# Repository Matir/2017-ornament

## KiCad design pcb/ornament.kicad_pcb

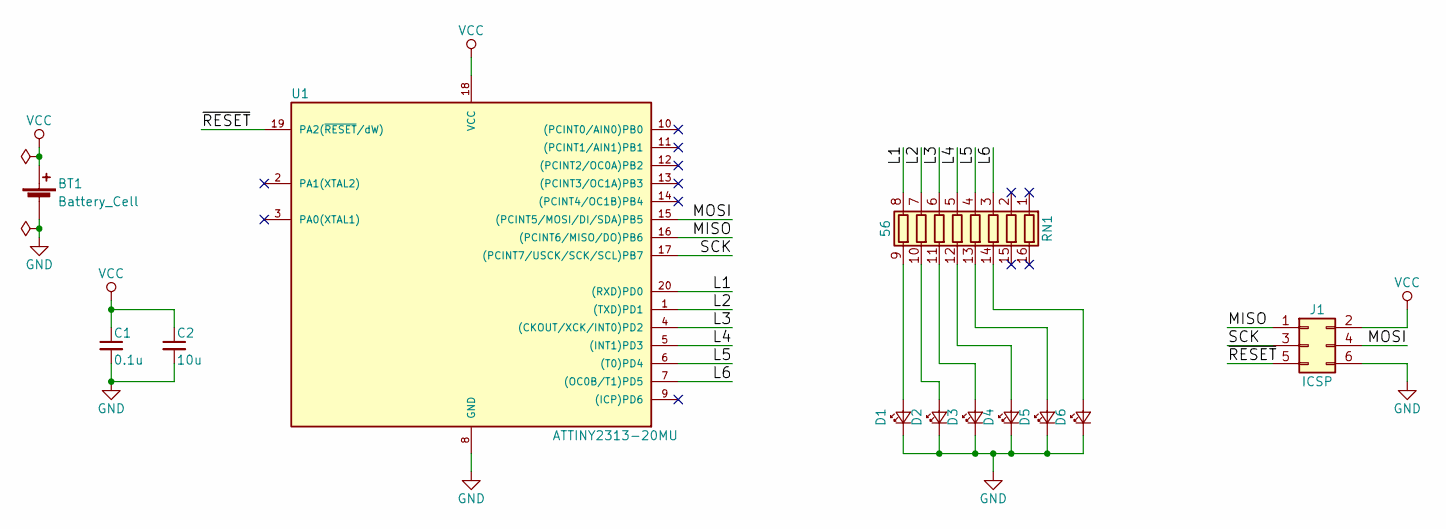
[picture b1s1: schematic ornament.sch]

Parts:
BT1: Battery_Cell; BAT_HLD
C1: 0.1u; C_0805
C2: 10u; C_0805
D1, D2, D3, D4, D5, D6: LED_Small; LED_0805
J1: ICSP; Pin_Header_Straight_2x03_Pitch2.54mm_SMD
RN1: 56; R_Array_Convex_8x0602
U1: ATTINY2313-20MU; QFN-20-1EP_4x4mm_Pitch0.5mm

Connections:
/L1: RN1.8 (R8.1), U1.20 ((RXD)PD0)
/L2: RN1.7 (R7.1), U1.1 ((TXD)PD1)
/L3: RN1.6 (R6.1), U1.4 ((CKOUT/XCK/INT0)PD2)
/L4: RN1.5 (R5.1), U1.5 ((INT1)PD3)
/L5: RN1.4 (R4.1), U1.6 ((T0)PD4)
/L6: RN1.3 (R3.1), U1.7 ((OC0B/T1)PD5)
/MISO: J1.1, U1.16 ((PCINT6/MISO/DO)PB6)
/MOSI: J1.4, U1.15 ((PCINT5/MOSI/DI/SDA)PB5)
/SCK: J1.3, U1.17 ((PCINT7/USCK/SCK/SCL)PB7)
/~RESET: J1.5, U1.19 (PA2(~RESET~/dW))
GND: BT1.2 (-), C1.2, C2.2, D1.1 (K), D2.1 (K), D3.1 (K), D4.1 (K), D5.1 (K), D6.1 (K), J1.6, U1.8 (GND), U1.21
unnamed: D1.2 (A), RN1.9 (R8.2)
unnamed: D2.2 (A), RN1.10 (R7.2)
unnamed: D3.2 (A), RN1.11 (R6.2)
unnamed: D4.2 (A), RN1.12 (R5.2)
unnamed: D5.2 (A), RN1.13 (R4.2)
unnamed: D6.2 (A), RN1.14 (R3.2)
VCC: BT1.1 (+), C1.1, C2.1, J1.2, U1.18 (VCC)

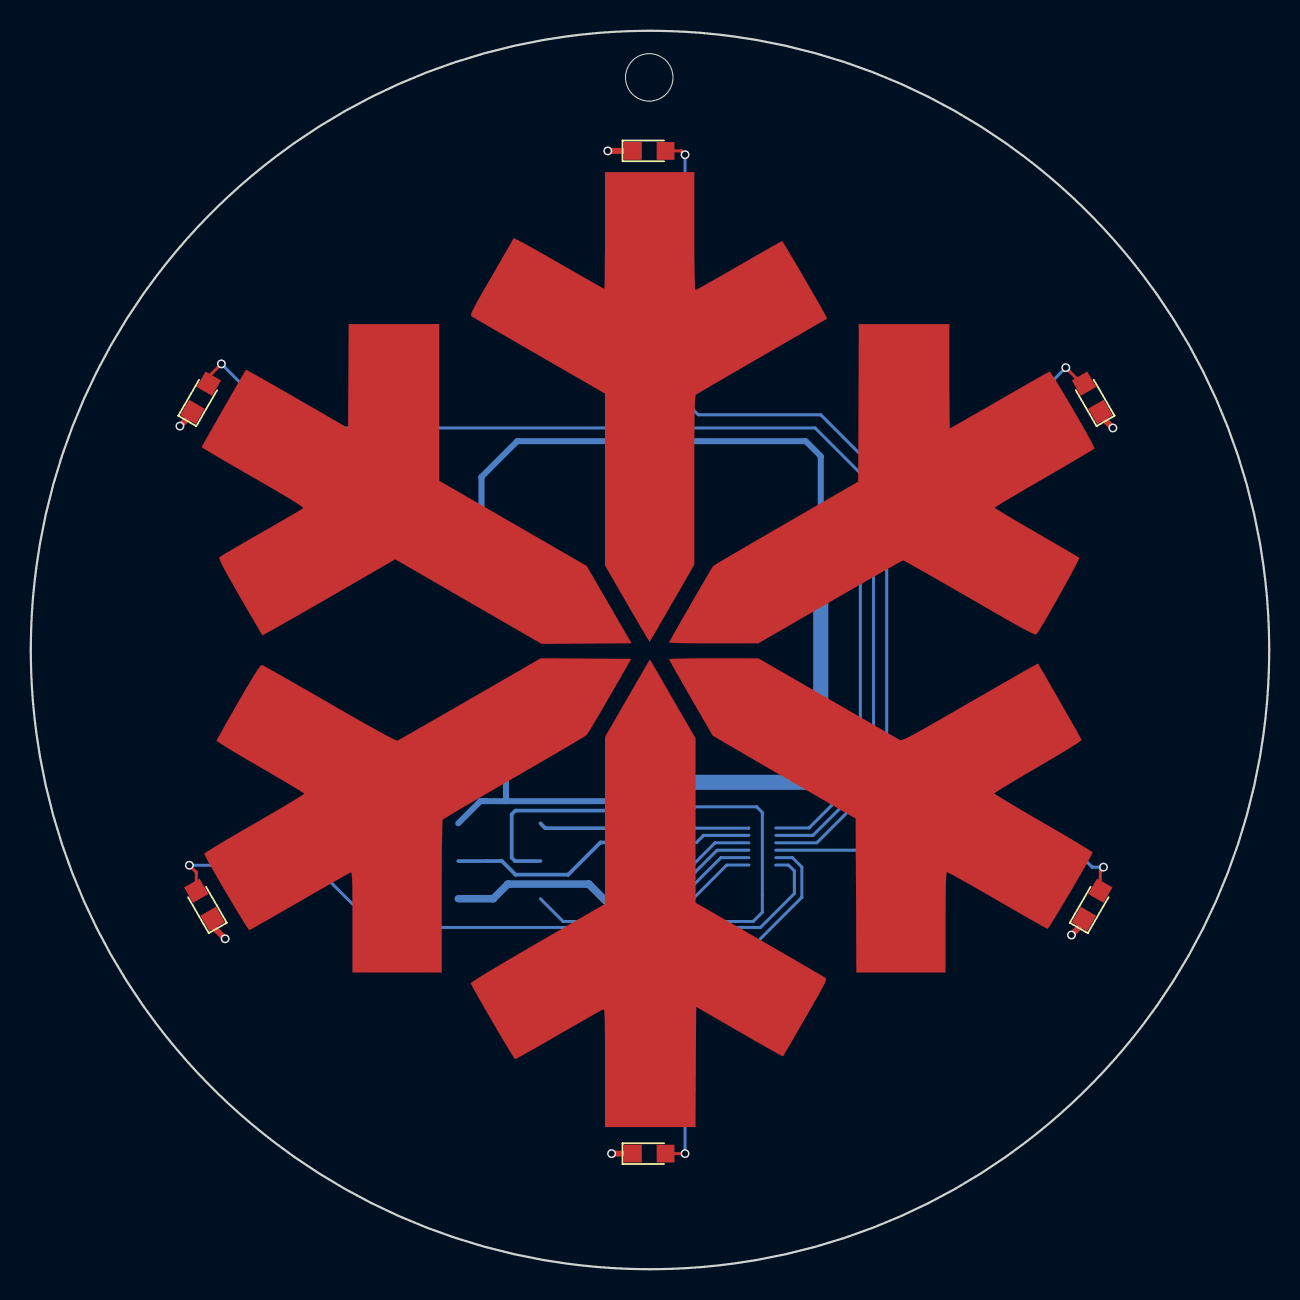
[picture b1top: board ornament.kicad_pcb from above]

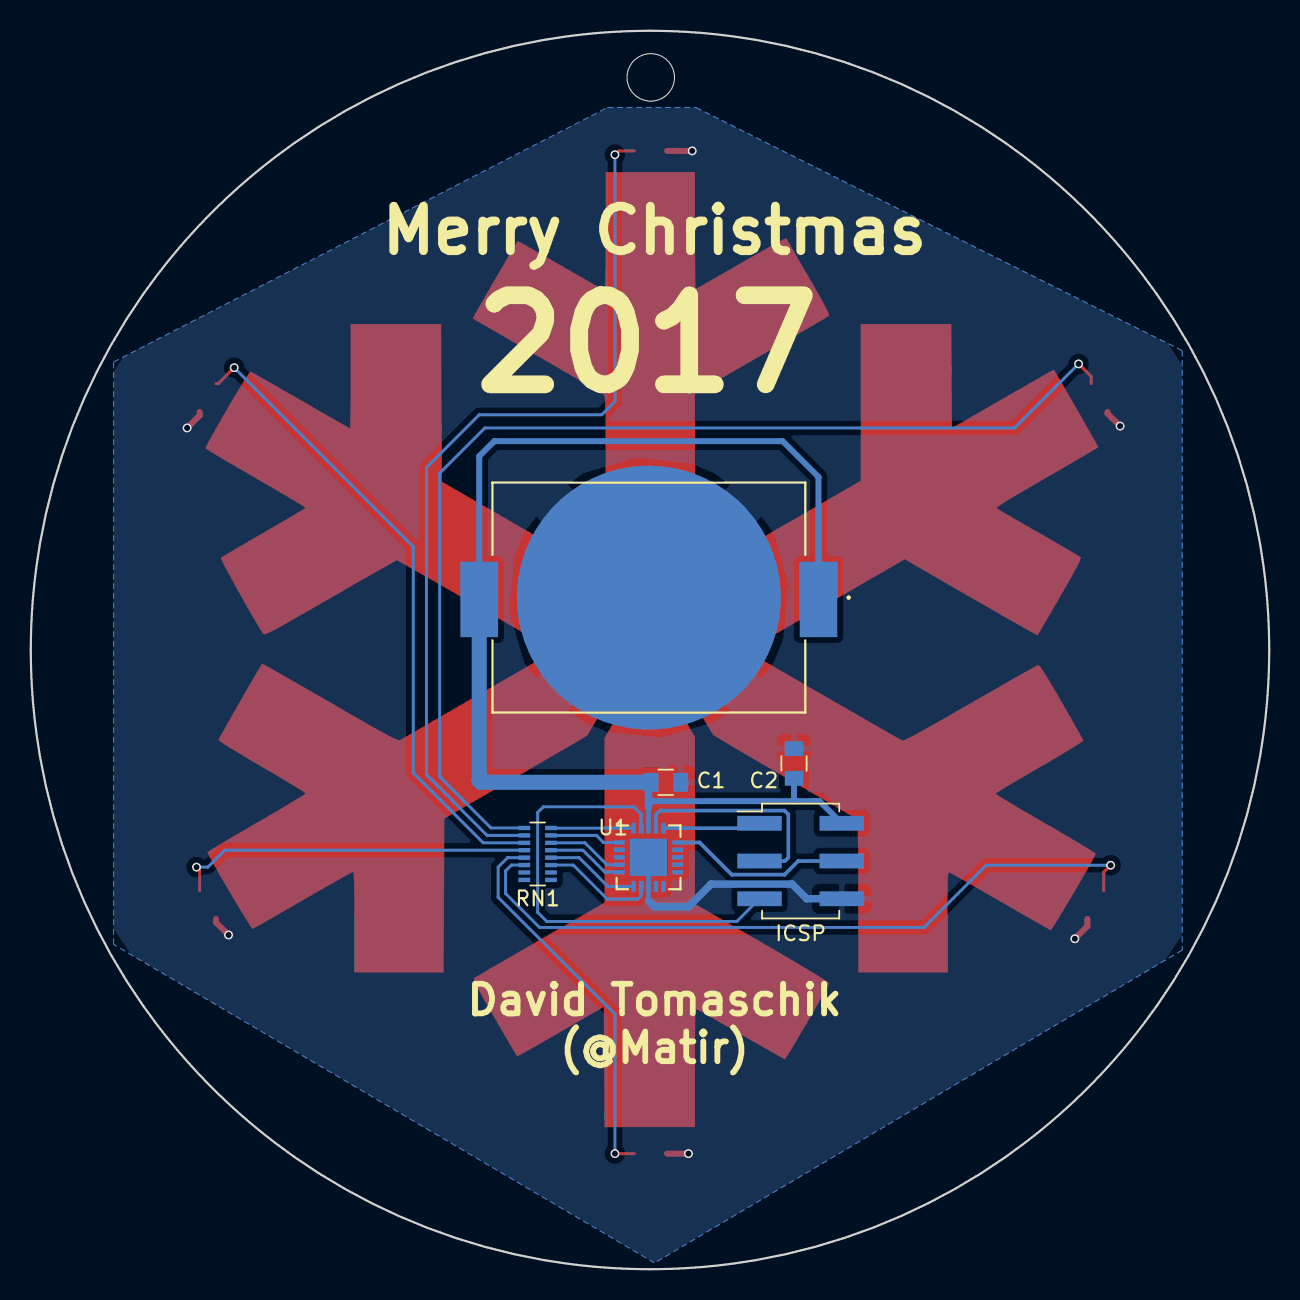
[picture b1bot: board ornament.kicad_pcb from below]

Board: 2 copper layers, 83.4 x 83.4 mm, 12 parts (6 on the bottom side), 18 nets.

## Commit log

2017-11-12 Initial setup, ready to produce.
2017-11-13 First attempt at firmware -- too slow.
2017-11-13 Remove commits.
2017-11-13 Fix prototype.
2017-11-13 Faster but less tunable firmware.
2017-11-17 Update board.
2017-11-19 Add silkscreen.
2017-11-19 Thicker traces.
2017-11-19 Add interlock to guarantee 3 LEDs at a time.
2017-11-21 Add avrdude support, gamma table.
2017-11-21 Update gamma correction.
2017-11-23 Update.
2017-12-07 Brightness change.

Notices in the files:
parts and their libraries:
Copyright 2016 Accelerated Designs. All rights reserved.
